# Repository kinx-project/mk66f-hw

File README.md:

This repository contains the hardware design files for the kinX mk66f keyboard
controller, a replacement controller for the Kinesis Advantage keyboard.

You can order this PCB at [OSH Park](https://oshpark.com/shared_projects/75qdnpC4).

You can order the components at [Mouser](https://www.mouser.ch/ProjectManager/ProjectDetail.aspx?AccessID=a9afbb88bc)

Note that the bootloader chip `IC_MKL04Z32_TQFP32` is not included in the BOM
and is only available from PJRC’s shop: https://www.pjrc.com/store/ic_mkl02.html

Also note that micro USB cables are not included in the BOM (you’ll need one for
power and firmware flashing, another one for USBHS data). I recommend building
the kinX hub, whose BOM includes the USB cables and which is a drop-in
replacement for the hub that comes in the Kinesis Advantage keyboard:
https://github.com/kinx-project/hub-hw

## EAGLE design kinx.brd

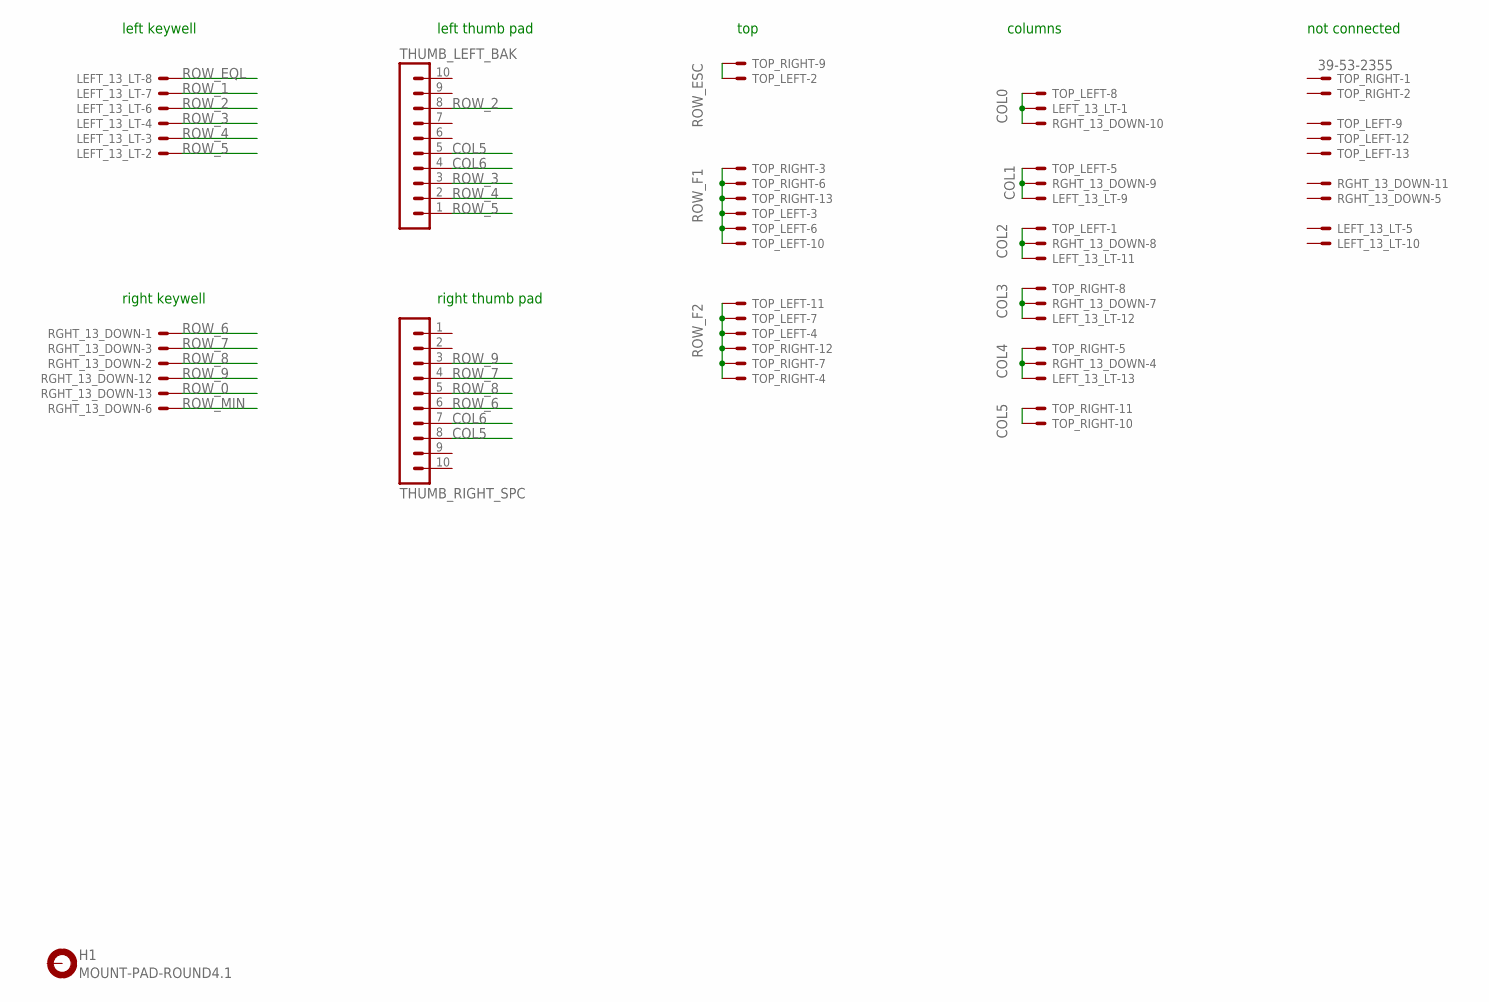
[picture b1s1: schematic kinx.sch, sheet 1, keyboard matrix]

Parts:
H1: MOUNT-PAD-ROUND4.1; 4,1-PAD
LEFT_13_LT: 39-53-2355; 39-53-2135; DIGIKEY WM14526-ND
RGHT_13_DOWN: 39-53-2355; 39-53-2135; DIGIKEY WM14526-ND
THUMB_LEFT_BAK: MA10-1
THUMB_RIGHT_SPC: MA10-1
TOP_LEFT: 39-53-2355; 39-53-2135; DIGIKEY WM14526-ND
TOP_RIGHT: 39-53-2355; 39-53-2135; DIGIKEY WM14526-ND

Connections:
COL0: LEFT_13_LT.P$1, RGHT_13_DOWN.P$10, TOP_LEFT.P$8; also elsewhere on the board
COL1: LEFT_13_LT.P$9, RGHT_13_DOWN.P$9, TOP_LEFT.P$5; also elsewhere on the board
COL2: LEFT_13_LT.P$11, RGHT_13_DOWN.P$8, TOP_LEFT.P$1; also elsewhere on the board
COL3: LEFT_13_LT.P$12, RGHT_13_DOWN.P$7, TOP_RIGHT.P$8; also elsewhere on the board
COL4: LEFT_13_LT.P$13, RGHT_13_DOWN.P$4, TOP_RIGHT.P$5; also elsewhere on the board
COL5: THUMB_LEFT_BAK.5, THUMB_RIGHT_SPC.8, TOP_RIGHT.P$10, TOP_RIGHT.P$11; also elsewhere on the board
COL6: THUMB_LEFT_BAK.4, THUMB_RIGHT_SPC.7; also elsewhere on the board
ROW_0: RGHT_13_DOWN.P$13; also elsewhere on the board
ROW_1: LEFT_13_LT.P$7; also elsewhere on the board
ROW_2: LEFT_13_LT.P$6, THUMB_LEFT_BAK.8; also elsewhere on the board
ROW_3: LEFT_13_LT.P$4, THUMB_LEFT_BAK.3; also elsewhere on the board
ROW_4: LEFT_13_LT.P$3, THUMB_LEFT_BAK.2; also elsewhere on the board
ROW_5: LEFT_13_LT.P$2, THUMB_LEFT_BAK.1; also elsewhere on the board
ROW_6: RGHT_13_DOWN.P$1, THUMB_RIGHT_SPC.6; also elsewhere on the board
ROW_7: RGHT_13_DOWN.P$3, THUMB_RIGHT_SPC.4; also elsewhere on the board
ROW_8: RGHT_13_DOWN.P$2, THUMB_RIGHT_SPC.5; also elsewhere on the board
ROW_9: RGHT_13_DOWN.P$12, THUMB_RIGHT_SPC.3; also elsewhere on the board
ROW_EQL: LEFT_13_LT.P$8; also elsewhere on the board
ROW_ESC: TOP_LEFT.P$2, TOP_RIGHT.P$9; also elsewhere on the board
ROW_F1: TOP_LEFT.P$3, TOP_LEFT.P$6, TOP_LEFT.P$10, TOP_RIGHT.P$3, TOP_RIGHT.P$6, TOP_RIGHT.P$13; also elsewhere on the board
ROW_F2: TOP_LEFT.P$4, TOP_LEFT.P$7, TOP_LEFT.P$11, TOP_RIGHT.P$4, TOP_RIGHT.P$7, TOP_RIGHT.P$12; also elsewhere on the board
ROW_MIN: RGHT_13_DOWN.P$6; also elsewhere on the board

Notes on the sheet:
left keywell
right keywell
left thumb pad
right thumb pad
columns
not connected
top

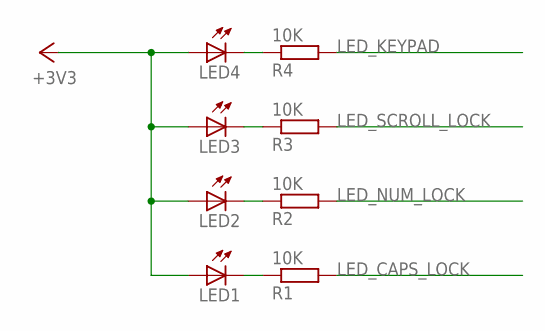
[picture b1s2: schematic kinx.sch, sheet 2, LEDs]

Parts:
LED1, LED2, LED3, LED4: LEDSML1206; SML1206
R1, R2, R3, R4: 10K; R1206

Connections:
+3V3: LED1.A, LED2.A, LED3.A, LED4.A; also elsewhere on the board
LED_CAPS_LOCK: R1.2; also elsewhere on the board
LED_KEYPAD: R4.2; also elsewhere on the board
LED_NUM_LOCK: R2.2; also elsewhere on the board
LED_SCROLL_LOCK: R3.2; also elsewhere on the board
unnamed: LED4.C, R4.1
unnamed: LED3.C, R3.1
unnamed: LED2.C, R2.1
unnamed: LED1.C, R1.1

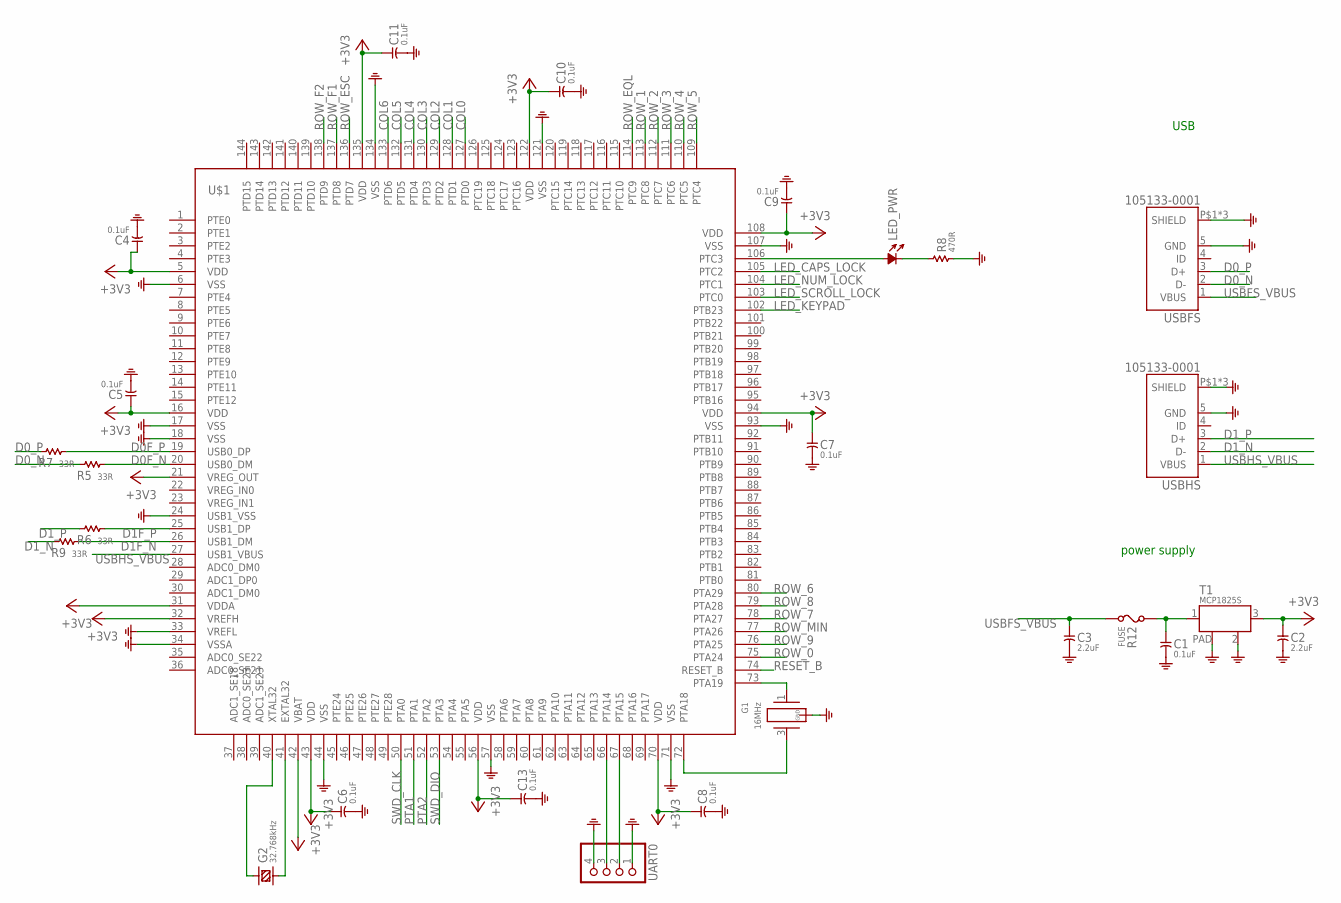
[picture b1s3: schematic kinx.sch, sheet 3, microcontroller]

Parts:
C1, C4, C5, C6, C7, C8, C9, C10, C11, C13: 0.1uF; C0603
C2, C3: 2.2uF; C0805
G1: 16MHz; FHXXX; DIGIKEY SER4068CT-ND
G2: 32.768kHz; TC26H
LED_PWR: LED; LED-0805
R5, R6, R7, R9: 33R; R0603
R8: 470R; R0603
R12: FUSE; F0805; DIGIKEY 507-1813-1-ND
T1: MCP1825S; SOT-223; DIGIKEY MCP1825S-3302E/DB-ND
U$1: MK66FX1M0VLQ18; TQFP144; DIGIKEY 568-13334-ND
UART0: PINHD-1X4/90; 1X04/90
USBFS: 105133-0001; MOLEX_105133-0001; DIGIKEY WM10134CT-ND
USBHS: 105133-0001; MOLEX_105133-0001; DIGIKEY WM10134CT-ND

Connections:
+3V3: C2.1, C4.1, C5.1, C6.1, C7.1, C8.1, C9.1, C10.1, C11.1, C13.1, T1.3 (OUT), U$1.5 (VDD), U$1.16 (VDD), U$1.21 (VREG_OUT), U$1.31 (VDDA), U$1.32 (VREFH), U$1.42 (VBAT), U$1.43 (VDD), U$1.56 (VDD), U$1.70 (VDD), U$1.94 (VDD), U$1.108 (VDD), U$1.122 (VDD), U$1.135 (VDD); also elsewhere on the board
COL0: U$1.127 (PTD0); also elsewhere on the board
COL1: U$1.128 (PTD1); also elsewhere on the board
COL2: U$1.129 (PTD2); also elsewhere on the board
COL3: U$1.130 (PTD3); also elsewhere on the board
COL4: U$1.131 (PTD4); also elsewhere on the board
COL5: U$1.132 (PTD5); also elsewhere on the board
COL6: U$1.133 (PTD6); also elsewhere on the board
D0F_N: R5.2, U$1.20 (USB0_DM)
D0F_P: R7.2, U$1.19 (USB0_DP)
D0_N: R5.1, USBFS.2 (D-)
D0_P: R7.1, USBFS.3 (D+)
D1F_N: R9.2, U$1.26 (USB1_DM)
D1F_P: R6.2, U$1.25 (USB1_DP)
D1_N: R9.1, USBHS.2 (D-)
D1_P: R6.1, USBHS.3 (D+)
GND: C1.2, C2.2, C3.2, C4.2, C5.2, C6.2, C7.2, C8.2, C9.2, C10.2, C11.2, C13.2, G1.2 (GND), G1.4 (GND), R8.1, T1.2 (GND), T1.PAD, U$1.6 (VSS), U$1.17 (VSS), U$1.18 (VSS), U$1.24 (USB1_VSS), U$1.33 (VREFL), U$1.34 (VSSA), U$1.44 (VSS), U$1.57 (VSS), U$1.71 (VSS), U$1.93 (VSS), U$1.107 (VSS), U$1.121 (VSS), U$1.134 (VSS), UART0.1, UART0.4, USBFS.5 (GND), USBFS.P$1 (SHIELD), USBFS.P$2 (SHIELD), USBFS.P$3 (SHIELD), USBHS.5 (GND), USBHS.P$1 (SHIELD), USBHS.P$2 (SHIELD), USBHS.P$3 (SHIELD); also elsewhere on the board
LED_CAPS_LOCK: U$1.105 (PTC2); also elsewhere on the board
LED_KEYPAD: U$1.102 (PTB23); also elsewhere on the board
LED_NUM_LOCK: U$1.104 (PTC1); also elsewhere on the board
LED_SCROLL_LOCK: U$1.103 (PTC0); also elsewhere on the board
unnamed: C1.1, R12.2, T1.1 (IN)
unnamed: G1.1, U$1.73 (PTA19)
unnamed: G1.3 (2), U$1.72 (PTA18)
unnamed: G2.2 (1), U$1.40 (XTAL32)
unnamed: G2.1 (2), U$1.41 (EXTAL32)
unnamed: LED_PWR.+, U$1.106 (PTC3)
unnamed: LED_PWR.-, R8.2
PTA1: U$1.51 (PTA1); also elsewhere on the board
PTA2: U$1.52 (PTA2); also elsewhere on the board
RESET_B: U$1.74 (RESET_B); also elsewhere on the board
ROW_0: U$1.75 (PTA24); also elsewhere on the board
ROW_1: U$1.113 (PTC8); also elsewhere on the board
ROW_2: U$1.112 (PTC7); also elsewhere on the board
ROW_3: U$1.111 (PTC6); also elsewhere on the board
ROW_4: U$1.110 (PTC5); also elsewhere on the board
ROW_5: U$1.109 (PTC4); also elsewhere on the board
ROW_6: U$1.80 (PTA29); also elsewhere on the board
ROW_7: U$1.78 (PTA27); also elsewhere on the board
ROW_8: U$1.79 (PTA28); also elsewhere on the board
ROW_9: U$1.76 (PTA25); also elsewhere on the board
ROW_EQL: U$1.114 (PTC9); also elsewhere on the board
ROW_ESC: U$1.136 (PTD7); also elsewhere on the board
ROW_F1: U$1.137 (PTD8); also elsewhere on the board
ROW_F2: U$1.138 (PTD9); also elsewhere on the board
ROW_MIN: U$1.77 (PTA26); also elsewhere on the board
RX: U$1.67 (PTA15), UART0.2
SWD_CLK: U$1.50 (PTA0); also elsewhere on the board
SWD_DIO: U$1.53 (PTA3); also elsewhere on the board
TX: U$1.66 (PTA14), UART0.3
USBFS_VBUS: C3.1, R12.1, USBFS.1 (VBUS)
USBHS_VBUS: U$1.27 (USB1_VBUS), USBHS.1 (VBUS)
VREG_IN0: U$1.22 (VREG_IN0)
VREG_IN1: U$1.23 (VREG_IN1)

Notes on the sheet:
USB
power supply

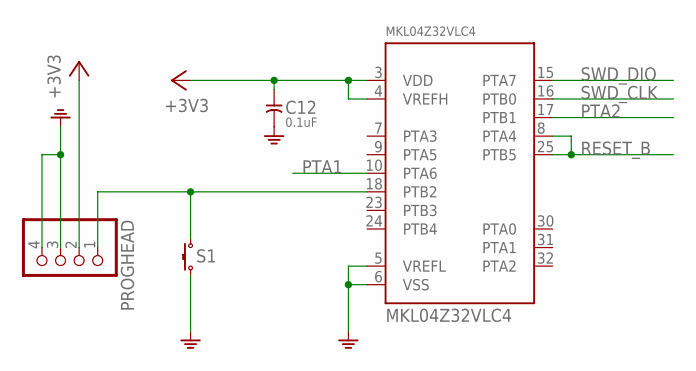
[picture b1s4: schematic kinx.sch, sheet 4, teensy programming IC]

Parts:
C12: 0.1uF; C0603
MKL04Z32VLC4: MKL04Z32VLC4; LQFP32-08
PROGHEAD: PINHD-1X4/90; 1X04/90
S1: TACT_SWITCH; ALPS_SKHH

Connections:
+3V3: C12.1, MKL04Z32VLC4.3 (VDD), MKL04Z32VLC4.4 (VREFH), PROGHEAD.2; also elsewhere on the board
GND: C12.2, MKL04Z32VLC4.5 (VREFL), MKL04Z32VLC4.6 (VSS), PROGHEAD.3, PROGHEAD.4, S1.3, S1.4 (3); also elsewhere on the board
unnamed: MKL04Z32VLC4.18 (PTB2), PROGHEAD.1, S1.1, S1.2 (1)
PTA1: MKL04Z32VLC4.10 (PTA6); also elsewhere on the board
PTA2: MKL04Z32VLC4.17 (PTB1); also elsewhere on the board
RESET_B: MKL04Z32VLC4.8 (PTA4), MKL04Z32VLC4.25 (PTB5); also elsewhere on the board
SWD_CLK: MKL04Z32VLC4.16 (PTB0); also elsewhere on the board
SWD_DIO: MKL04Z32VLC4.15 (PTA7); also elsewhere on the board

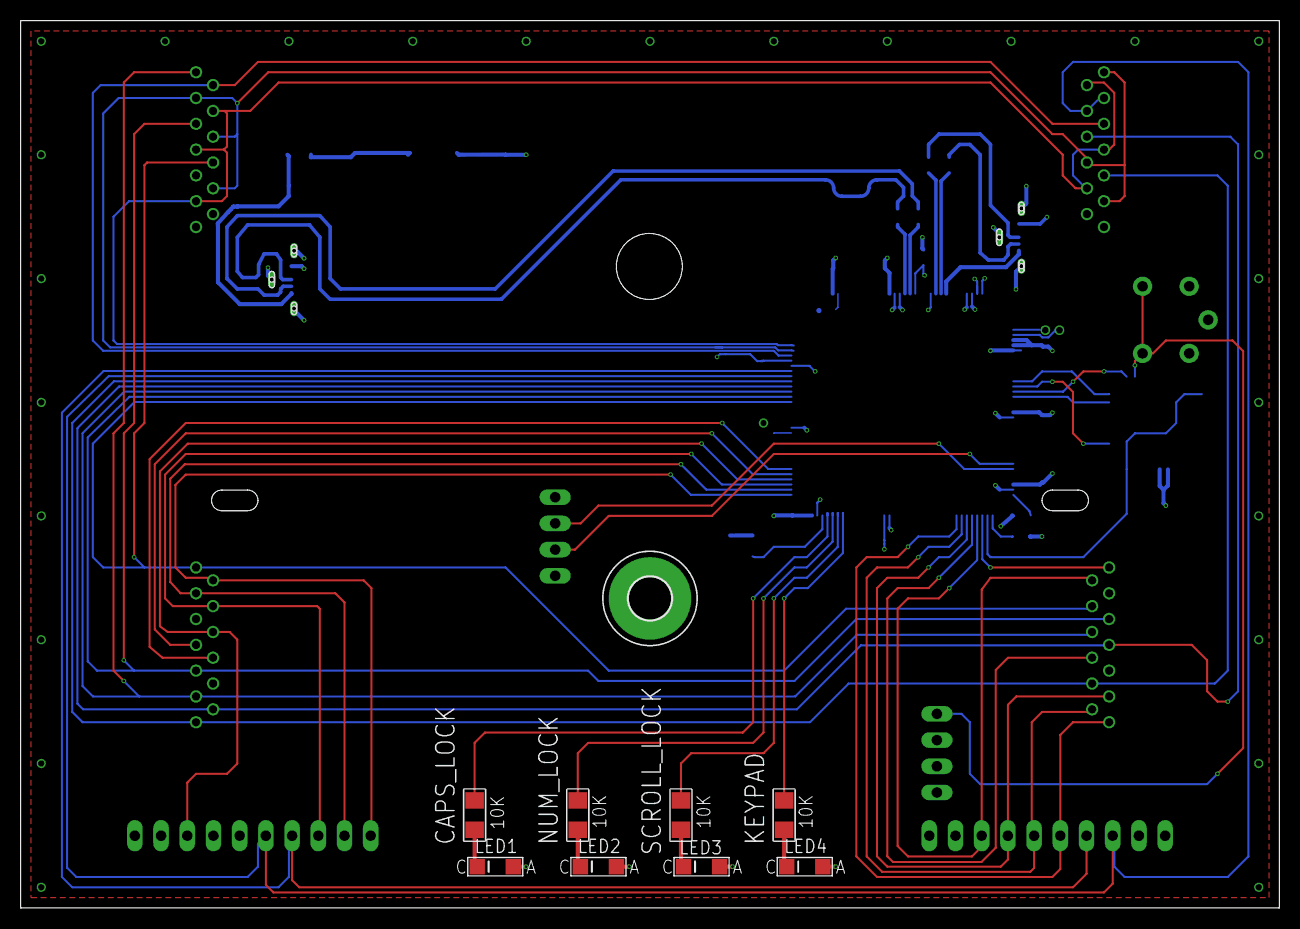
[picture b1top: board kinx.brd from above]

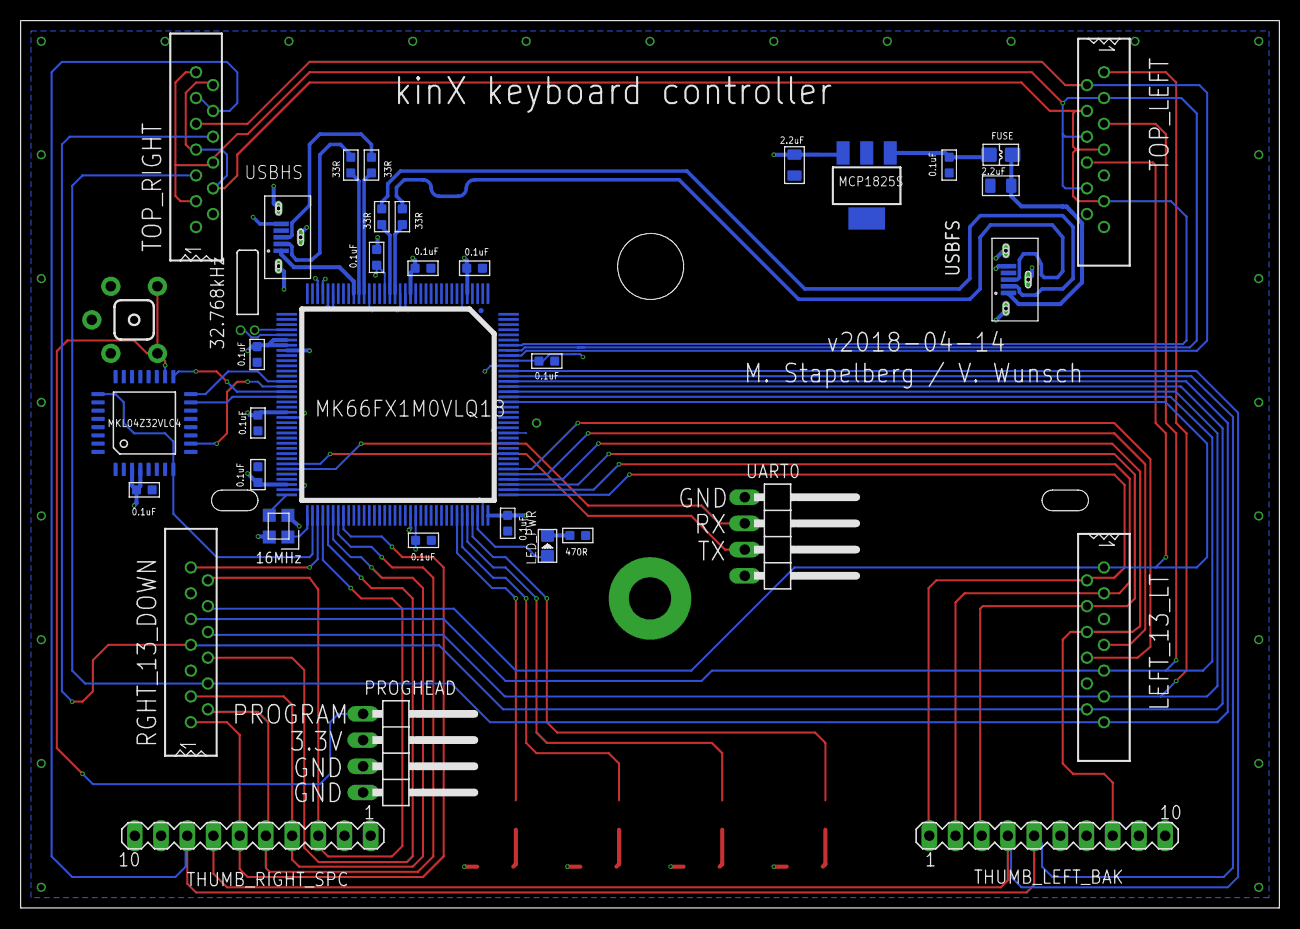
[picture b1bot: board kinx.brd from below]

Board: 4 copper layers, 121.9 x 85.9 mm, 45 parts (36 on the bottom side), 57 nets.

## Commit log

2018-03-27 Connect remaining VSS pins
2018-03-27 Switch USB connector from Würth (1.0mm PCB) to Molex (1.5mm PCB)
    The Würth ones are incompatible with our PCB thickness — they can just barely be
    soldered, and are loose after just a few connections.
2018-03-27 fix silkscreen for 0.1μF capacitor
2018-03-27 fix the molex connector library from snapeda
2018-03-27 put LED resistor value on the silkscreen
2018-03-27 Add MK66FX1M0VLQ18-based kinX controller version
2018-03-27 Fix Molex connector pads
    As per the PCB layout from the drawing:
    http://www.molex.com/pdm_docs/sd/1051330001_sd.pdf
2018-03-27 use 10K resistors to drive the LEDs
2018-03-27 fix silk screen for USB ports
2018-03-27 move via for clearance
2018-03-27 route the new USB connectors, rotate so that angled cables fit
2018-03-27 Enlarge crystal pads for easier soldering
2018-03-27 fix silkscreen for power LED
2018-03-27 Move vias for easier soldering
2018-03-27 fix MPN/OC_MOUSER for the molex 105133-0011 connectors
2018-03-27 fix ERC errors and approve okay errors
2018-03-27 enlarge LED pads for easier soldering
2018-03-27 better net names
2018-03-27 bump revision to v2018-02-11
2018-03-27 Switch to Molex 105133-0011 (USB 2.0 instead of USB)
2018-03-27 update version on silkscreen
2018-03-27 Clean up schematic (no board changes)
2018-03-27 Bugfix: wire up USB1_VBUS and all GND airwires
2018-03-27 silk screen: crystal: make orientation label visible again after pad enlargement
2018-03-27 silk screen: add resistor outlines on top layer
2018-03-27 silk screen: very very clearly mark LED cathode/anode
2018-03-27 add LED resistor order codes
2018-03-27 enlarge FUSE pads for easier soldering
2018-03-27 approve all remaining DRC errors, this is the best we can do
2018-04-14 Increase isolation of GND planes for better manufacturability
    Done using “change isolate 8mil” on both GND planes.
    A few previous PCBs had their ground plane accidentally connected to traces.
    OSH Park explained that this can be due to imbalances in the acid concentration,
    and advised to increase isolation.
2018-04-14 bump revision to v2018-04-14
2018-04-14 add mouser part number for the 10K resistors
2018-04-14 Change 0.1μF capacitors from 81-GRM39X104K16 to 80-C0603C104M4R7411
    The former is no longer available.
2018-04-14 add BOM to git
2018-04-14 add note about the bootloader chip and USB cables
2018-04-17 add oshpark link
2018-04-17 fix osh park spelling
2018-04-17 add mouser link
2019-05-10 update mouser cart to contain resistors, replace out-of-stock components
    fixes #1
